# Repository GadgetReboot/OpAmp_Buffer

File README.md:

# OpAmp_Buffer
Op Amp Input and Output buffer with Phone jacks for guitar effects prototyping
<br><br><BR><BR>

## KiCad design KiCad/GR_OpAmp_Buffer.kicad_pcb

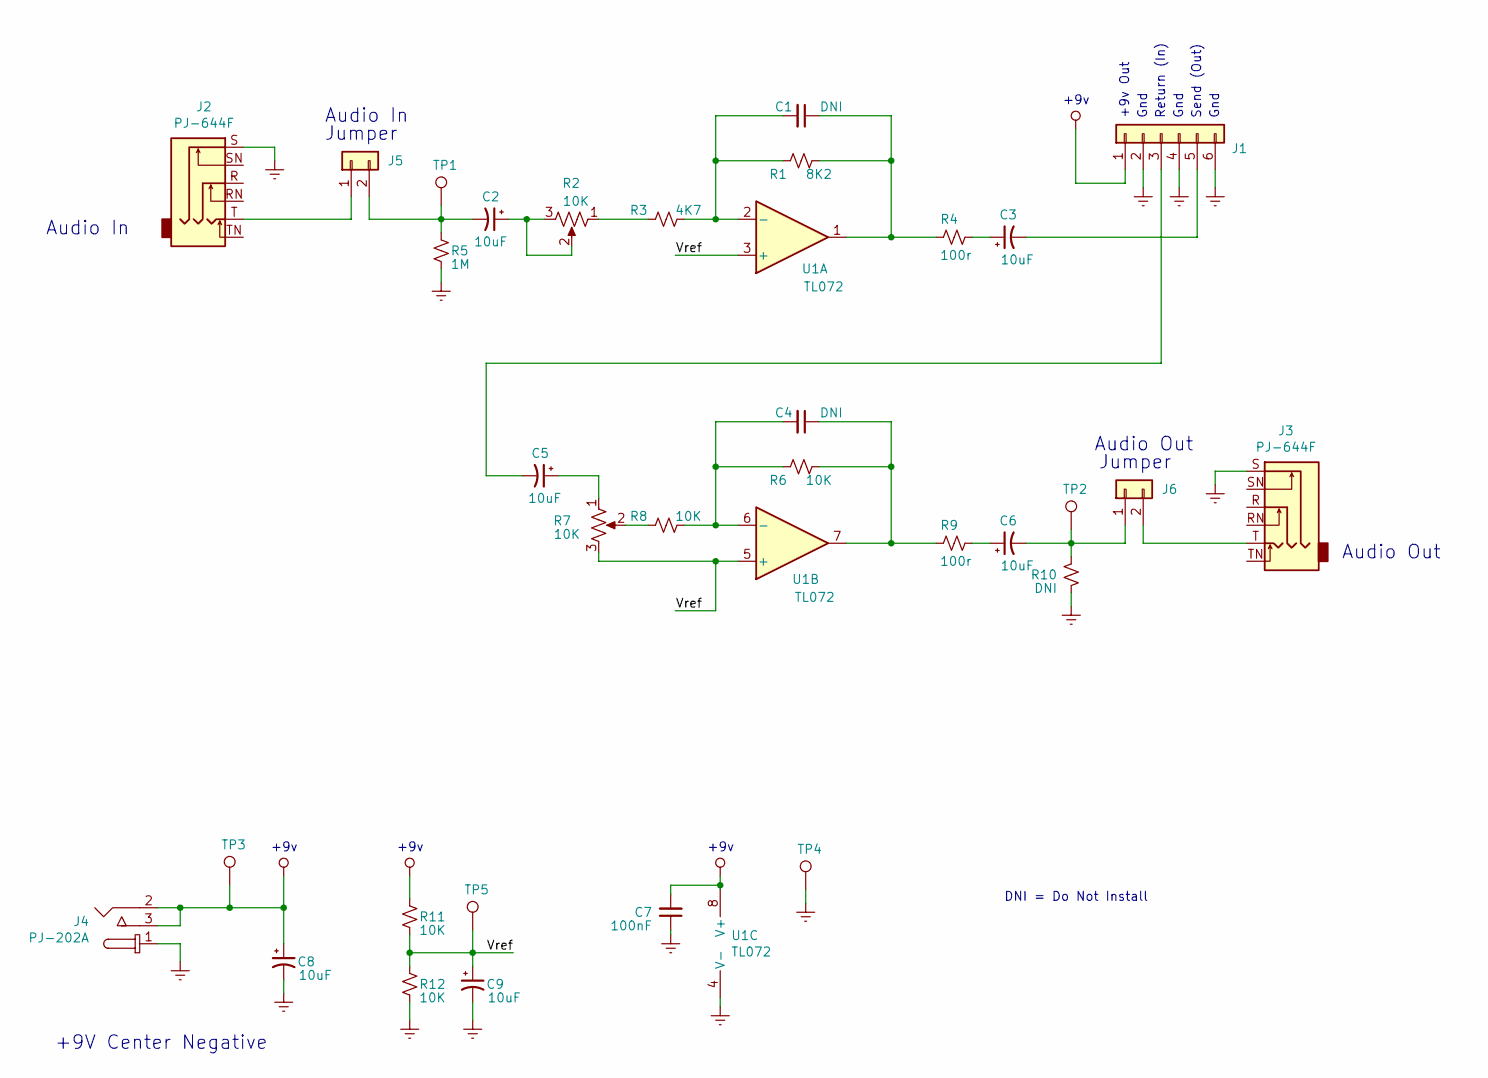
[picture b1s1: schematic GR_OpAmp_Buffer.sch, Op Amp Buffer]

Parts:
C1, C4: DNI; C_Disc_D5.0mm_W2.5mm_P2.50mm
C2, C3, C5, C6, C8, C9: 10uF; CP_Radial_D5.0mm_P2.50mm
C7: 100nF; C_Disc_D5.0mm_W2.5mm_P2.50mm
J1: Conn_01x06; PinHeader_1x06_P2.54mm_Vertical
J2, J3: PJ-644F; Jack_6.35mm_Neutrik_NMJ6HFD2_Horizontal
J4: PJ-202A; Barrel_Jack_5.5mmODx2.1mmID_PJ-202A; MPN PJ-202A; Digi-Key_PN CP-202A-ND
J5, J6: Conn_01x02; PinHeader_1x02_P2.54mm_Vertical
R1: 8K2; R_Axial_DIN0207_L6.3mm_D2.5mm_P10.16mm_Horizontal
R2, R7: 10K; Potentiometer_Bourns_PTV09A-1
R3: 4K7; R_Axial_DIN0207_L6.3mm_D2.5mm_P10.16mm_Horizontal
R4, R9: 100r; R_Axial_DIN0207_L6.3mm_D2.5mm_P10.16mm_Horizontal
R5: 1M; R_Axial_DIN0207_L6.3mm_D2.5mm_P10.16mm_Horizontal
R6, R8, R11, R12: 10K; R_Axial_DIN0207_L6.3mm_D2.5mm_P10.16mm_Horizontal
R10: DNI; R_Axial_DIN0207_L6.3mm_D2.5mm_P10.16mm_Horizontal
TP1, TP2, TP3, TP4, TP5: TestPoint; TestPoint_Loop_D1.80mm_Drill1.0mm_Beaded
U1: TL072; DIP-8_W7.62mm

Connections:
/Vref: C9.1, R7.3, R11.1, R12.2, TP5.1, U1.3 (+), U1.5 (+)
GNDREF: C7.1, C8.2, C9.2, J1.2, J1.4, J1.6, J2.S, J3.S, J4.1, R5.1, R10.1, R12.1, TP4.1, U1.4 (V-)
unnamed: C1.1, R1.1, R4.2, U1.1
unnamed: C1.2, R1.2, R3.1, U1.2 (-)
unnamed: C2.1, R2.2, R2.3
unnamed: C2.2, J5.2, R5.2, TP1.1
unnamed: C3.1, R4.1
unnamed: C3.2, J1.5
unnamed: C4.1, R6.1, R9.2, U1.7
unnamed: C4.2, R6.2, R8.1, U1.6 (-)
unnamed: C5.1, R7.1
unnamed: C5.2, J1.3
unnamed: C6.1, R9.1
unnamed: C6.2, J6.1, R10.2, TP2.1
unnamed: J2.T, J5.1
unnamed: J3.T, J6.2
unnamed: R2.1, R3.2
unnamed: R7.2, R8.2
VCC: C7.2, C8.1, J1.1, J4.2, J4.3, R11.2, TP3.1, U1.8 (V+)

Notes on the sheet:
DNI = Do Not Install
+9v
Gnd
+9v Out
Send (Out)
Return (In)
Audio In
Audio Out
+9V Center Negative
Jumper

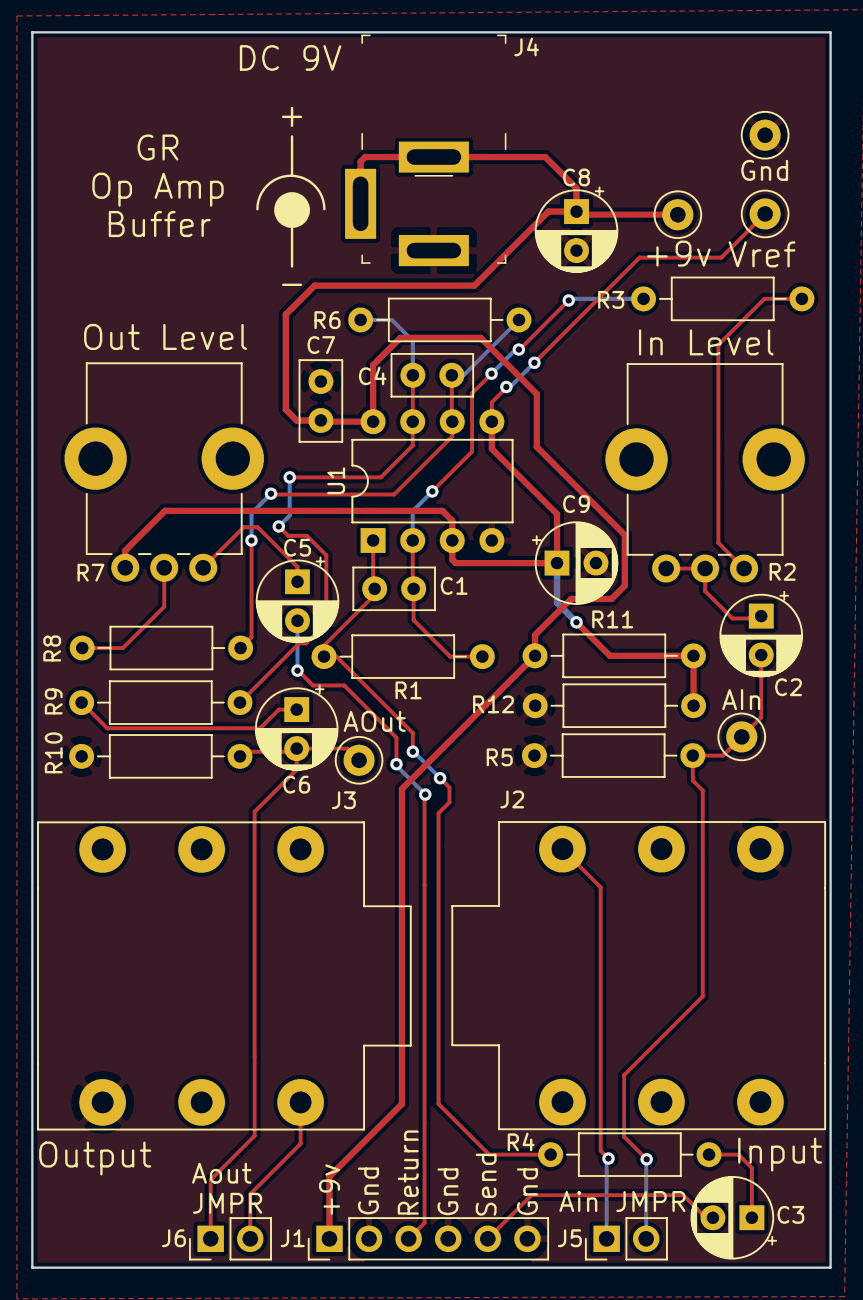
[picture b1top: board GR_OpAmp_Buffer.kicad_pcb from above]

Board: 2 copper layers, 51.2 x 79.2 mm, 33 parts (0 on the bottom side), 19 nets.
